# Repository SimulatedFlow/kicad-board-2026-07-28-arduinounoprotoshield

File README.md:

# 2026-07-28-arduinounoprotoshield

<!-- SF-STORE-BLOCK:BEGIN -->
## 🛒 Source-available — see before you buy

This repository contains the **full design files** of a commercial hardware board. It is **source-available, not open source**: read it, evaluate it, then buy a license to use it. See **LICENSE.md (source-available, purchase required)**.

**Get it / Buy:**
- **Order on eBay** (this board, bare PCB): https://www.ebay.de/itm/398223887818
- Product page (specs, photos, price): https://simulatedflow.teufel-engineering.com/platinen/2026-07-28-arduinounoprotoshield/
- eBay store — all our boards and PCB art: https://www.ebay.de/usr/simula-9
- Merch shop (dev & gaming): https://simulatedflow.myspreadshop.de
- Merch shop (Synthetica / EDM): https://synthetica.myspreadshop.de
- Direct / invoice (Simulated Flow UG): simulatedflow@gmail.com

### 📬 **Free Board Documentation & Firmware Pack**

Schematics, BOMs and example-firmware docs for our STM32 carrier boards. Get it by joining the newsletter — plus a heads-up when something new ships. Double opt-in, unsubscribe in one click, no address sharing.

👉 **[Get the free pack](https://simulatedflow.teufel-engineering.com/newsletter/hardware/?q=gh)**

_© 2026 Simulated Flow UG. All rights reserved._
<!-- SF-STORE-BLOCK:END -->

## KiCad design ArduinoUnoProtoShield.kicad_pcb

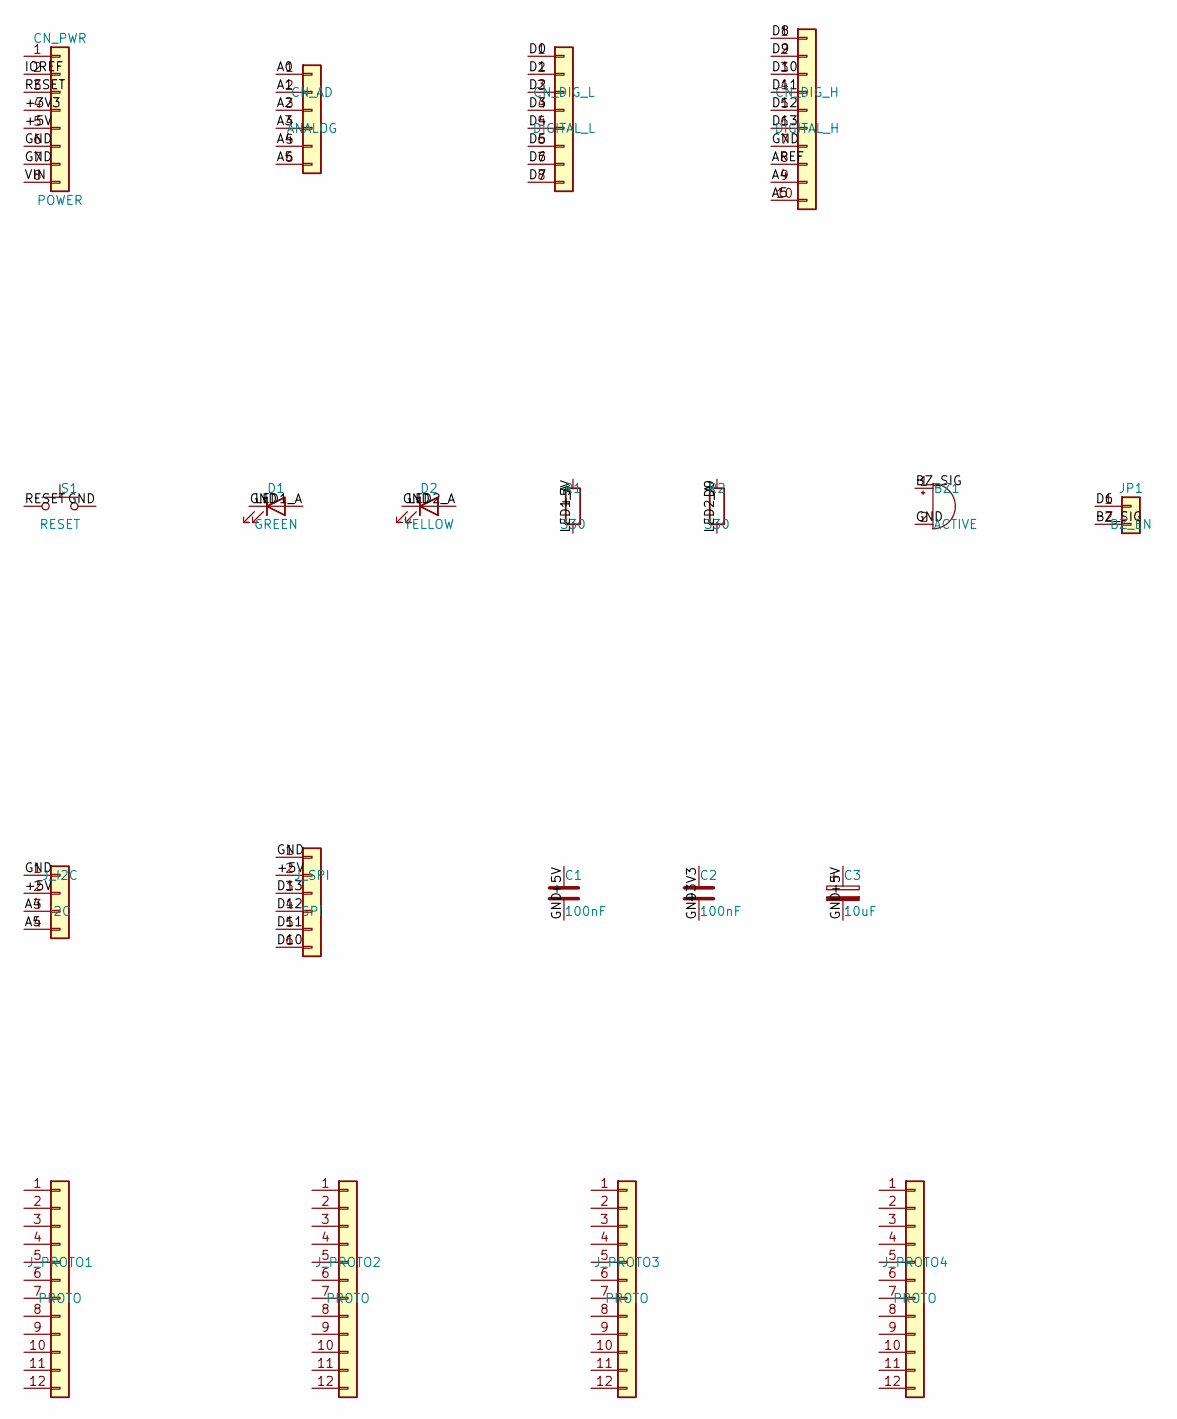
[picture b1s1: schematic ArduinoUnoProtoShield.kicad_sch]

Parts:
BZ1: ACTIVE; Buzzer_12x9.5RM7.6
C1, C2: 100nF; C_Disc_D5.0mm_W2.5mm_P5.00mm
C3: 10uF; CP_Radial_D5.0mm_P2.00mm
CN_AD: ANALOG; PinSocket_1x06_P2.54mm_Vertical
CN_DIG_H: DIGITAL_H; PinSocket_1x10_P2.54mm_Vertical
CN_DIG_L: DIGITAL_L; PinSocket_1x08_P2.54mm_Vertical
CN_PWR: POWER; PinSocket_1x08_P2.54mm_Vertical
D1: GREEN; LED_D5.0mm
D2: YELLOW; LED_D5.0mm
JP1: BZ_EN; PinHeader_1x02_P2.54mm_Vertical
J_I2C: I2C; PinHeader_1x04_P2.54mm_Vertical
J_PROTO1, J_PROTO2, J_PROTO3, J_PROTO4: PROTO; PinHeader_1x12_P2.54mm_Vertical
J_SPI: SPI; PinHeader_1x06_P2.54mm_Vertical
R1, R2: 330; R_Axial_DIN0207_L6.3mm_D2.5mm_P7.62mm_Horizontal
S1: RESET; SW_PUSH_6mm_H5mm

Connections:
+3V3: C2.1, CN_PWR.4
+5V: C1.1, C3.1, CN_PWR.5, J_I2C.2, J_SPI.2, R1.1
A0: CN_AD.1
A1: CN_AD.2
A2: CN_AD.3
A3: CN_AD.4
A4: CN_AD.5, CN_DIG_H.9, J_I2C.3
A5: CN_AD.6, CN_DIG_H.10, J_I2C.4
AREF: CN_DIG_H.8
BZ_SIG: BZ1.1 (+), JP1.2
D0: CN_DIG_L.1
D1: CN_DIG_L.2
D2: CN_DIG_L.3
D3: CN_DIG_L.4
D4: CN_DIG_L.5
D5: CN_DIG_L.6
D6: CN_DIG_L.7, JP1.1
D7: CN_DIG_L.8
D8: CN_DIG_H.1
D9: CN_DIG_H.2, R2.1
D10: CN_DIG_H.3, J_SPI.6
D11: CN_DIG_H.4, J_SPI.5
D12: CN_DIG_H.5, J_SPI.4
D13: CN_DIG_H.6, J_SPI.3
GND: BZ1.2 (-), C1.2, C2.2, C3.2, CN_DIG_H.7, CN_PWR.6, CN_PWR.7, D1.1 (K), D2.1 (K), J_I2C.1, J_SPI.1, S1.2
IOREF: CN_PWR.2
LED1_A: D1.2 (A), R1.2
LED2_A: D2.2 (A), R2.2
RESET: CN_PWR.3, S1.1
VIN: CN_PWR.8

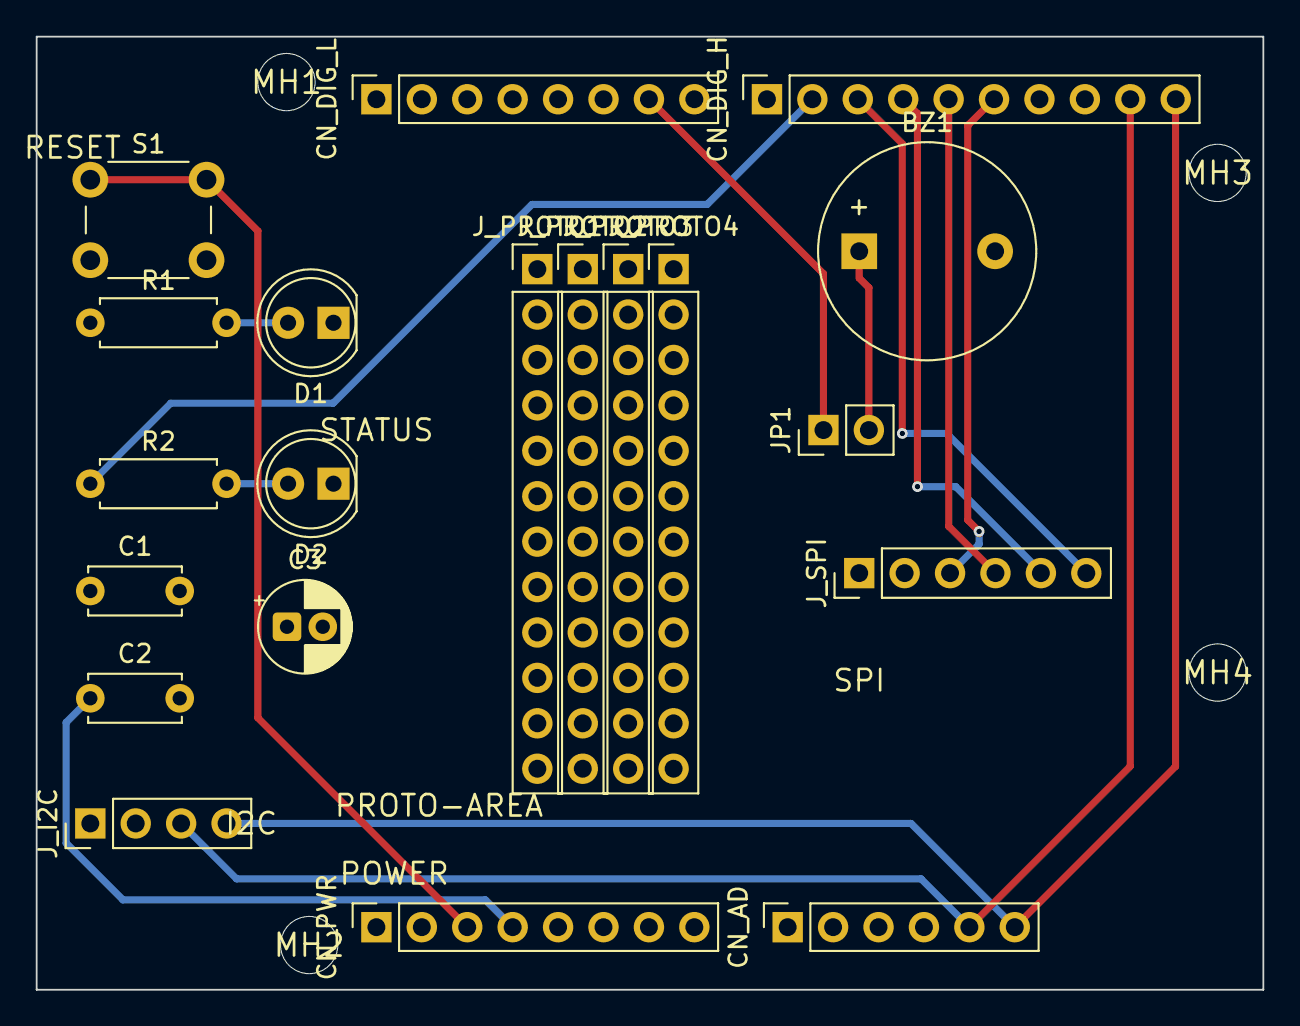
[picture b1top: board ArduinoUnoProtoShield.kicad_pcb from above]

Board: 4 copper layers, 68.6 x 53.3 mm, 24 parts (0 on the bottom side), 15 nets.

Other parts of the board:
MH1, MH2, MH3, MH4: MountingHole_3.2mm
